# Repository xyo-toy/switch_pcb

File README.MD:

# Information
From the following datasheet :
http://ww1.microchip.com/downloads/en/devicedoc/atmel-7766-8-bit-avr-atmega16u4-32u4_datasheet.pdf

## Datasheet sections
Crystal information: p30
Usb related info: p256-259
Information about decoupling capacitors and some components values: "Electrical characteristics"
Boot related info : p80, p340
Reset info : p50-54
Decoupling Capacitor : p306, p307

## Components list

-- 1 ATMega32u4 : https://www.digikey.fr/en/products/detail/microchip-technology/ATMEGA32U4-AUR/3440960
-- 1 Crystal: https://www.digikey.com/product-detail/en/epson/FA-238-16.0000MB-C3/SER3686CT-ND/2403459
-- 2 22pF Capacitors: https://www.digikey.com/product-detail/en/kemet/C0805C220J5GACTU/399-1113-1-ND/411388
-- 4 0.1uF Capacitors: https://www.digikey.com/product-detail/en/yageo/CC0805ZRY5V9BB104/311-1361-1-ND/2103145
-- 1 1uF Capacitors: https://www.digikey.com/product-detail/en/yageo/CC0805KKX7R7BB105/311-1365-1-ND/2103149
-- 1 4.7uF Capacitors: https://www.digikey.com/product-detail/en/murata-electronics-north-america/GRM21BR61E475KA12L/490-3335-1-ND/702876
-- 1 10uF Capacitors: https://www.digikey.com/en/products/detail/yageo/CC0805ZKY5V6BB106/2103093
-- 2 22 Ohm Resistors: https://www.digikey.com/product-detail/en/stackpole-electronics-inc/RMCF0805JT22R0/RMCF0805JT22R0CT-ND/1942533
-- 2 10k Ohm Resistors: https://www.digikey.com/product-detail/en/stackpole-electronics-inc/RMCF0805JT10K0/RMCF0805JT10K0CT-ND/1942577
-- 4 Diodes: https://www.digikey.com/product-detail/en/micro-commercial-co/1N4148W-TP/1N4148WTPMSCT-ND/717311
-- 1 Button: https://www.digikey.com/product-detail/en/e-switch/TL3342F160QG-TR/EG2531CT-ND/379004
-- 1 Mini USB Connector: https://www.digikey.com/product-detail/en/hirose-electric-co-ltd/UX60SC-MB-5S8/H11589CT-ND/1949225

## Net informations
https://electronics.stackexchange.com/questions/424912/how-can-i-program-an-atmega32u4-over-usb-with-this-schematic

## Other references
https://github.com/ruiqimao/keyboard-pcb-guide

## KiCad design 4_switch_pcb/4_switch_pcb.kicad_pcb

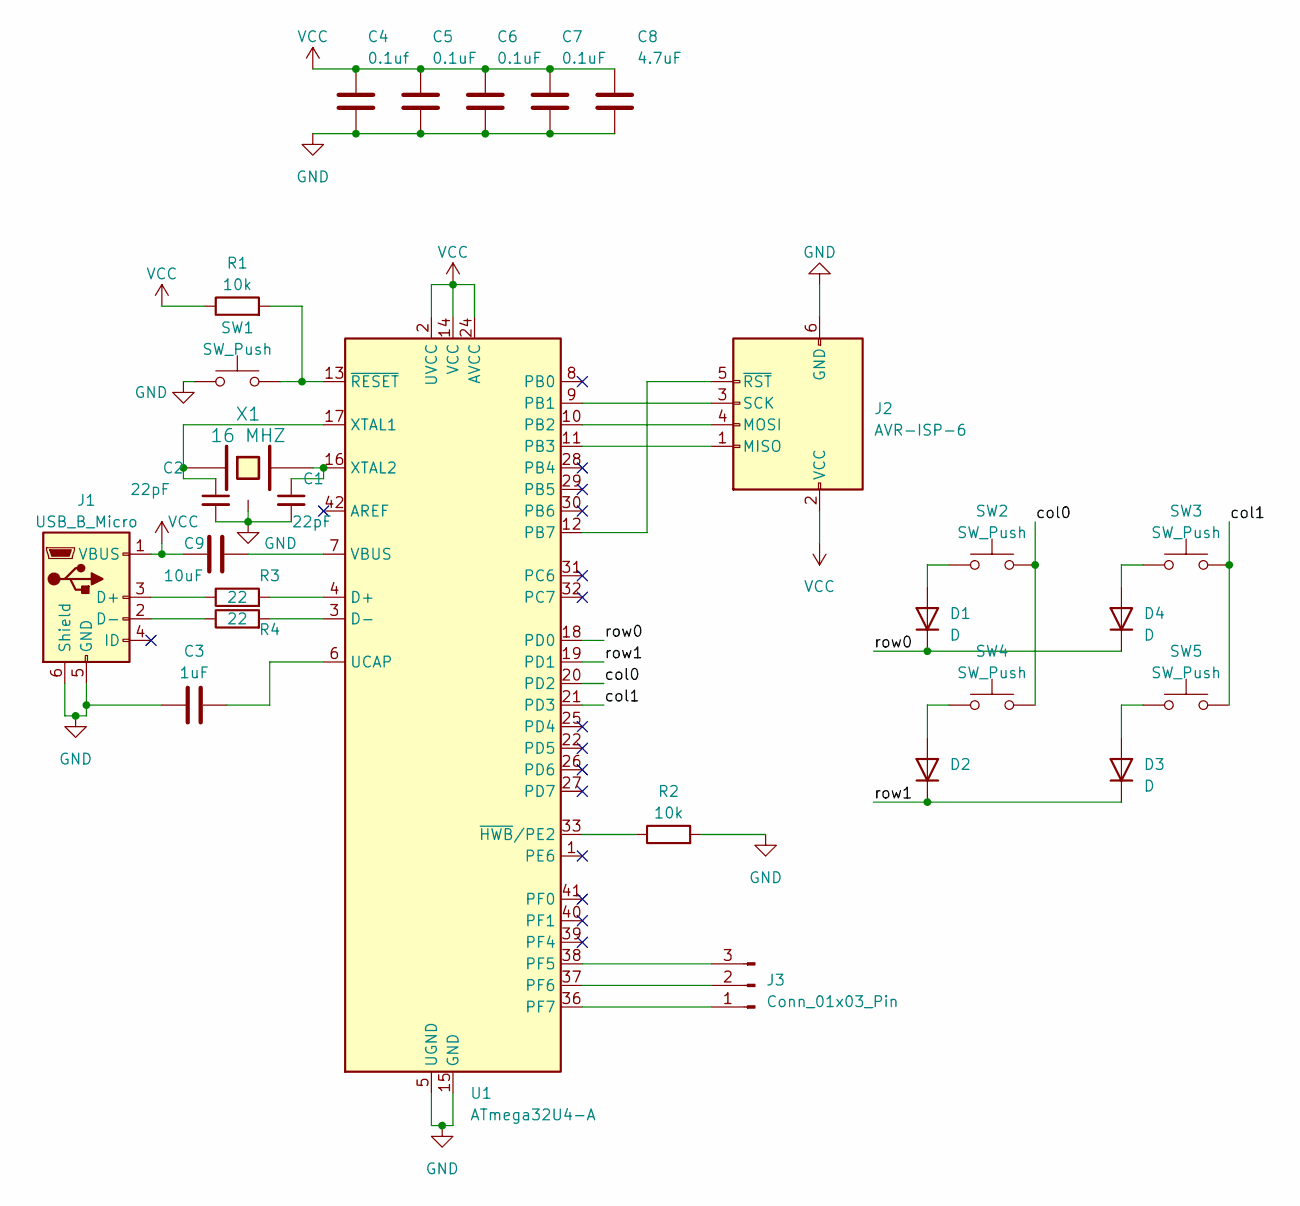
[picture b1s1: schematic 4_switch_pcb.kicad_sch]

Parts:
C1, C2: 22pF; C_0805_2012Metric_Pad1.18x1.45mm_HandSolder
C3: 1uF; C_0805_2012Metric_Pad1.18x1.45mm_HandSolder
C4: 0.1uf; C_0805_2012Metric_Pad1.18x1.45mm_HandSolder
C5, C6, C7: 0.1uF; C_0805_2012Metric_Pad1.18x1.45mm_HandSolder
C8: 4.7uF; C_0805_2012Metric_Pad1.18x1.45mm_HandSolder
C9: 10uF; C_0805_2012Metric_Pad1.18x1.45mm_HandSolder
D1, D2, D3, D4: D; D_SOD123_axial
J1: USB_B_Micro; USB_miniB_hirose_5S8
J2: AVR-ISP-6
J3: Conn_01x03_Pin; PinHeader_1x03_P1.00mm_Vertical_SMD_Pin1Right
R1, R2: 10k; R_0805_2012Metric_Pad1.20x1.40mm_HandSolder
R3, R4: 22; R_0805_2012Metric_Pad1.20x1.40mm_HandSolder
SW1: SW_Push; SW_SPST_TL3342
SW2, SW3, SW4, SW5: SW_Push; SW_Cherry_MX_1.00u_PCB
U1: ATmega32U4-A; TQFP-44_10x10mm_P0.8mm
X1: 16 MHZ; crystal_FA238-TSX3225

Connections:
/col0: SW2.2, SW4.2, U1.20 (PD2)
/col1: SW3.2, SW5.2, U1.21 (PD3)
/row0: D1.1 (K), D4.1 (K), U1.18 (PD0)
/row1: D2.1 (K), D3.1 (K), U1.19 (PD1)
GND: C1.2, C2.2, C3.1, C4.2, C5.2, C6.2, C7.2, C8.2, J1.5 (GND), J1.6 (Shield), J2.6 (GND), R2.2, SW1.1, U1.5 (UGND), U1.15 (GND), U1.23 (GND), U1.35 (GND), U1.43 (GND), X1.3
unnamed: D1.2 (A), SW2.1
unnamed: D2.2 (A), SW4.1
unnamed: D3.2 (A), SW5.1
unnamed: D4.2 (A), SW3.1
unnamed: J1.3 (D+), R3.1
unnamed: J1.2 (D-), R4.1
unnamed: J2.1 (MISO), U1.11 (PB3)
unnamed: J2.4 (MOSI), U1.10 (PB2)
unnamed: J2.3 (SCK), U1.9 (PB1)
unnamed: J2.5 (~RST), U1.12 (PB7)
unnamed: J3.1, U1.36 (PF7)
unnamed: J3.2, U1.37 (PF6)
unnamed: J3.3, U1.38 (PF5)
unnamed: R3.2, U1.4 (D+)
unnamed: R4.2, U1.3 (D-)
unnamed: C3.2, U1.6 (UCAP)
unnamed: C9.2, U1.7 (VBUS)
unnamed: C2.1, U1.17 (XTAL1), X1.1
unnamed: C1.1, U1.16 (XTAL2), X1.2
unnamed: R2.1, U1.33 (~HWB/PE2)
unnamed: R1.2, SW1.2, U1.13 (~RESET)
VCC: C4.1, C5.1, C6.1, C7.1, C8.1, C9.1, J1.1 (VBUS), J2.2 (VCC), R1.1, U1.2 (UVCC), U1.14 (VCC), U1.24 (AVCC), U1.34 (VCC), U1.44 (AVCC)

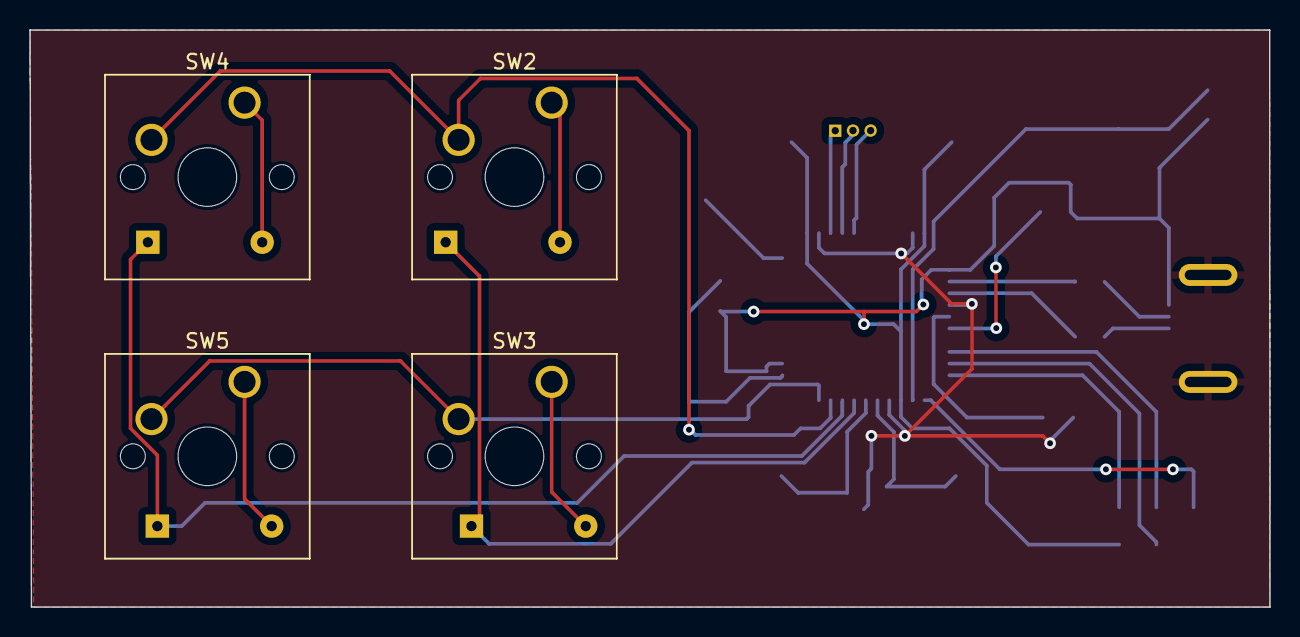
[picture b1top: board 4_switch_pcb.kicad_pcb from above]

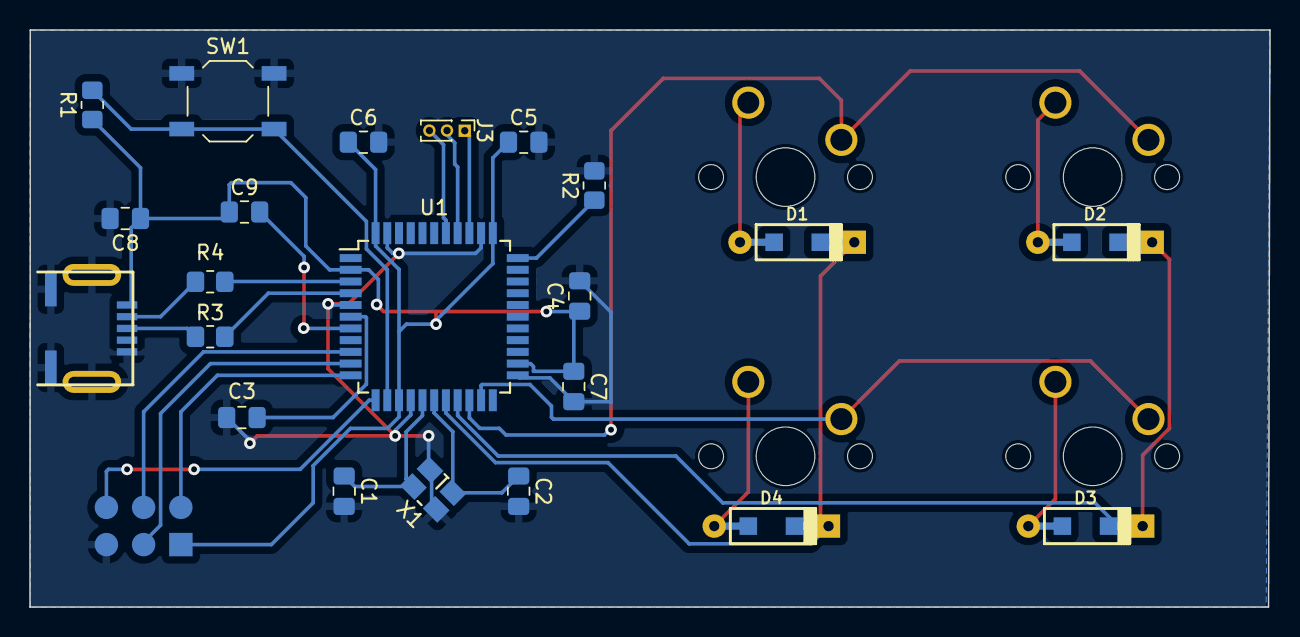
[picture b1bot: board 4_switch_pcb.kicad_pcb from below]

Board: 2 copper layers, 84.6 x 39.4 mm, 27 parts (23 on the bottom side), 27 nets.

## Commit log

2023-04-07 init repo
2023-04-10 Add external ref in README
2023-04-16 feat: add switch matrix, isp and header pins
2023-04-18 feat: add decoupling value, missing vusb capa, crystal frequency
2023-04-18 feat: update component list
2023-04-19 feat: add footprints selection
2023-04-26 component alignement
2023-04-28 add base of routing
2023-04-28 base of pcb edition
2023-04-28 pcb finish
2023-04-28 change component list
2023-04-28 generate file to send
2023-04-29 add explication sheet and migration BOM to excel
